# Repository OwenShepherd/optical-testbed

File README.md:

# AWESoMe Automation
Team: **A**pparatus for **W**avefront **E**rror **S**ens**o**r **Me**asurement

Website: [AWESoMe](https://www.colorado.edu/aerospace/current-students/undergraduates/senior-design-projects/past-senior-projects/2017-2018/apparatus)  

AWESoMe is a joint project between the South West Research Institute (SWRI) and a team of Aerospace Engineering students at Boulder.  The goal of the project is to create a testbed for comparing the performance of a [Shack-Hartmann Array](https://en.wikipedia.org/wiki/Shack%E2%80%93Hartmann_wavefront_sensor) (SHA) and a [Roddier Curvature Wavefront Sensor](http://www.soft.belastro.net/files/tmp/Wave-front_reconstruction_from_defocused_images_and_the_testing_of_ground-based_optical_telescopes.pdf) (RCWS).  

This repository contains .NET programs aimed at automating as much of the testbed as possible due to the large number of tests that need to be run in a timely manner.  This mostly includes: prompting the user to load in a specifically formatted CSV for scheduling tests, and then running those tests one-by-one by adjusting the parameters of the SHA, RCWS, and motorized stages.

## Getting Started
Some third-party drivers and Visual Studio 15 need to be installed.

### Pre-Requisites  
**Please download drivers as 32-bit or it may cause some compatibility issues**  

First, ensure you have at least Visual Studio 15 installed (or at least 10.0.40219.1).  Then, install the following drivers in the listed order:
- [ASI120MM Drivers](http://astronomy-imaging-camera.com/software/)
- [ASCOM Platform 6.3](https://ascom-standards.org/Downloads/Index.htm)
- [ASCOM Platform Developer Components](https://ascom-standards.org/Downloads/PlatDevComponents.htm)
- [ASI Cameras ASCOM Driver](http://astronomy-imaging-camera.com/software/)
- [QHY Camera Driver](http://www.qhyccd.com/QHY5-III-Camera.html)
- [QHY ASCOM Driver (Capture Version V0131)](http://www.qhyccd.com/ASCOM-Camera.html)

Next, in order to use the complete version of the program, the most recent version of Python (At least Python version 3.6) must be installed:
- [Python Downloads](https://www.python.org/downloads/)

Then, install pyserial for Python 3 in any fashion (reccomended to use pip); just ensure that pyserial can be called from a Python 3 program:
- [Pyserial](https://pypi.python.org/pypi/pyserial)

Next, the program requires extra DLLs in order to run properly.  These must be acquired by also installing the following software:
- [Thorlabs Kinesis (32-bit for 32-bit or 32-bit for 64-bit](https://www.thorlabs.com/software_pages/ViewSoftwarePage.cfm?Code=Motion_Control&viewtab=0)
- [Thorlabs WFS](https://www.thorlabs.com/software_pages/ViewSoftwarePage.cfm?Code=WFS)

Lastly, it is possible that the software will initially have issues connecting to the QHY due to a defect in the driver.  In this event, it is required to use sharpcap to connect to the QHY via ASCOM, and simply set the gain to, say, 1, and click accept.  It is possible that some error warnings will pop up, but ignore these.  Try running your experiment again and see if an error still pops up about some camera connection issues.
- [Sharpcap](https://www.sharpcap.co.uk/sharpcap/downloads)

## Running the Program
As of now, the program has been tested with all components of the testbed and is working in its designed fashion for data collection.  The most recent working version of the program is contained in the "TestBed_Automation_Final" Visual Studio Project.  The installer for the project builds may be found at [this link](https://drive.google.com/open?id=1Bk6WBR5vOVbcDDSYLsn6n1ccp4iNH_cr) (NOTE: Only CU Boulder Accounts may access this link).

### Using the Executable
The Visual Studio Project will automatically add the required files for the executable to the appropriate directory.  But, when running the executable outside of visual studio, ensure that the following are in the same directory as the EXE:
- ASCOM.DeviceInterfaces.dll
- ASCOM.DriverAccess.dll
- ASCOM.Exceptions.dll
- ASCOM.Utilities.dll
- SerialReader.py
- Thorlabs.MotionControl.DeviceManager.dll
- Thorlabs.MotionControl.DeviceManagerCLI.dll
- Thorlabs.MotionControl.GenericMotorCLI.dll
- Thorlabs.MotionControl.KCube.DCServo.dll
- Thorlabs.MotionControl.KCube.DCServoCLI.dll
- Thorlabs.MotionControl.Tools.Common.dll
- Thorlabs.MotionControl.Tools.Logging.dll
- Throlabs.WFS.Interop.dll

An official "release" hasn't been made yet for this program, although running the program in Visual Studio will achieve the desired results.

## Data Organization
This is how data is organized by the program.

### Filesystem Organization
Here is how data will be organized.  An experiment corresponds to a collection of data
taken during one session.  Each state corresponds to a different test (i.e. with
different de-focus distances, exposures, etc...).
```
EXAMPLE_EXPERIMENT
├── 2018_02_03_13_48_41_STATE1
├── 2018_02_03_13_50_55_STATE2
├── 2018_02_03_13_52_13_STATE3
├── 2018_02_03_13_54_32_STATE4
│   ├── data_RCWS
│   │   ├── img_RCWS_aft.png
│   │   ├── img_RCWS_fore.png
│   │   └── zernikes_RCWS.csv
│   ├── data_SHA
│   │   ├── img_SHA_aft.png
│   │   ├── img_SHA_fore.png
│   │   ├── spt_SHA_aft.png
│   │   ├── spt_SHA_fore.png
│   │   ├── wft_SHA_aft.png
│   │   ├── wft_SHA_fore.png
│   │   └── zernikes_SHA.csv
│   ├── env_data.csv
│   ├── state_parameters.csv
│   └── zernikes_model.csv
└── experiment_schedule.csv
```
The automation program will automatically create the experiment directory (as named off user input), and will automatically create the state folders based on the number of tests in the schedule file.  Each state folder will be filled with the appropriate data shown above as the tests are run.

### Schedule File Structure
The experiment_schedule.csv file will specify all the system states that are to be tested for a given experiment. For each state specified in this file the automated test control program will create the appropriate sub-folder of the test and populate it with the data that is produced while the experiment is running. In post-processing other files can be added in the created file structure. The first row will include the header:  
```
RCWS EXPT (us), SHA EXPT (us), RCWS D FORE (um), RCWS D AFT (um), M2 A X (arc sec), M2 A Y (arc sec)  
```
After that line every row of data will specify those state values at which to make a wavefront measurement with both sensors.

### Environmental Sensor Data
Data is collected from the environmental sensors and sent in an organized way to the computer.  Each set of data sent contains at most: 3-Dimensional readings from 6 accelerometers, and temperature readings from 6 IC temperature sensors.
```
| 0xA0 | 0xA1 | RT | SN | {PL} | SH | SL | MH | ML | UH | UL | CS | 0x0D | 0x0A |
```
These bytes / sets of bytes contain the following data:
- RT: (0 or 1) indicates whether the payload contains accelerometer or temperature data.
- SN: Indicates the sensor number / sensor ID
- PL: The actual sensor data; details below
- SH: MSB for seconds elapsed
- SL: LSB for seconds elapsed
- MH: MSB for milliseconds elapsed
- ML: LSB for milliseconds elapsed
- UH: MSB for microseconds elapsed
- UL: LSB for microseconds elapsed
- CS: Result of taking XOR of all payload and timestamp bytes.  AKA: A rudimentary checksum.

**Payload Organization**:  
Temperature Sensor:
```
| Temperature High Byte | Temperature Low Byte |
```

Accelerometer:
```
| Acc. Axis 1 H | Acc. Axis 1 L | Acc. Axis 2 H | Acc. Axis 2 L | Acc. Axis 3 H | Acc. Axis 3 L |
```

## Conceptual Information

### ASCOM References
The two RCWS cameras (ASI120MM & QHY...) both interface with Windows using ASCOM.  Some
references on how to use ASCOM with VS:
- [ASCOM Standards](http://www.ascom-standards.org/Help/Developer/html/7d9253c2-fdfd-4c0d-8225-a96bddb49731.htm)

### ASEN_RCWS class
The ASEN_RCWS class can be used to take images and save them in a very simple
way.  Currently, it has only been tested with the ASI, but should be able to
easily extend to the QHY if necessary.  To use the class, follow the current
example shown in the "program.cs" file for using the ASI120MM.

### ASEN_KDC Class
In order for the current test code for the KDC101 to work, you must do the
following.  Currently the class is not ready as further testing needs to be
completed.

Add these references to the program (if they are not already included):
- Thorlabs.MotionControl.KCube.DCServoCLI.dll
- Thorlabs.MotionControl.DeviceManagerCLI.dll
- Thorlabs.MotionControl.GenericMotorCLI.dll

In addition, the following native C DLLs need to be copied to the executable folder:
- ThorLabs.MotionControl.KCube.DCServo.dll
- ThorLabs.MotionControl.DeviceManager.dll

These DLL files may be found in the References_DLL/KDC101 folder.

## Authors (This Repository)
- Owen Shepherd
- Jake Crouse

## The Team
- Robert Belter
- Ali Colic
- Jake Crouse
- Lucas Droste
- Diego Gomes
- Ankit Hriday
- Owen Lyke
- Brandon Noirot
- Owen Shepherd
- Brandon Stetler

## Acknowledgements
- Eliot Young (SWRI)
- Bob Woodruff (SWRI)
- Engineering Excellence Fund (EEF)
- NASA Glenn

## ASEN 4018 - Senior Projects Environmental Sensors Code
This code was used to test the following devices and conduct experiments with
the following software as well as accelerometers and thermometers.

The code is located in root/env_sensors.

### Software Used
* Arduino IDE 1.8.5
* SDFat Version 1.0.3
* TeensyDuino Version 1.40
* DallasTemperature Version 3.7.6
* Python 3.6.2
* pySerial 3.4

### Software Downloads
* [Arduino IDE](https://www.arduino.cc/en/Main/Software)  
* [TeensyDuino](https://www.pjrc.com/teensy/td_download.html)  
* [SDFat Repository](https://github.com/greiman/SdFat)
* [pySerial](https://pypi.python.org/pypi/pyserial)
* [Python](https://www.python.org/downloads/)

### Installation
Download and install the Arduino IDE along with the TeensyDuino
addon.  Then, download SDFat Version 1.0.3 and DallasTemperature using the
library manager in the IDE, and then you can open "ASEN-4018-EnvSensors.ino"
located in the root directory using the Arduino IDE.  

To use the custom libraries made for the project, either
copy the folders in "LocalLib" to the Arduino libraries folder at the root of
your sketches directory or (what I did for easier git integration): create
symbolic links to the folders in "LocalLib" and place those shortcuts in the Arduino
libraries folder.  NOTE: This was mostly developed in Ubuntu; Windows users should 
note that shortcuts != symoblic links.  I have not tested development on a Apple
computer.

### Filesystem Info
Function details (.h) and their implementations (.cpp) are
located in their respective header and implementation files within "LocalLib/".
The current functions provide ADXL reading, SD Performance estimates, and SD
implementations.  

### Testing information
Please read "RateTesting.md" in the root of the git directory for information
about how to test the Teensy for various data rate performances.

### Examples Used to Develop Code
* [Speeding UP SD Writes](https://forum.arduino.cc/index.php?topic=49649.0)
* [Low-Latency Logger Example](https://github.com/greiman/SdFat/tree/master/examples/LowLatencyLogger)
* [Using an ADXL345 with the Teensy](https://gist.github.com/FuzzyWuzzie/b1903a8353dc1ec57da8)
* [Using DS18B20 Temp. Sensor with Arduino](https://create.arduino.cc/projecthub/TheGadgetBoy/ds18b20-digital-temperature-sensor-and-arduino-9cc806)

### Examples
To test Teensy SD read / write performance:
```
#include "TeensySDPerformance.h"

void setup() {
  perfSetup();
}

void loop() {
  perfLoop();
}  
```

To read temperature from pin 1 on the Teensy and save it to the SD card:
```
#include "temp.h"
#include <string>

String filename = "TemperatureReadings.csv";

void setup() {
  tempSetup();

}

void loop() {
  tempLoop(filename);
}
```

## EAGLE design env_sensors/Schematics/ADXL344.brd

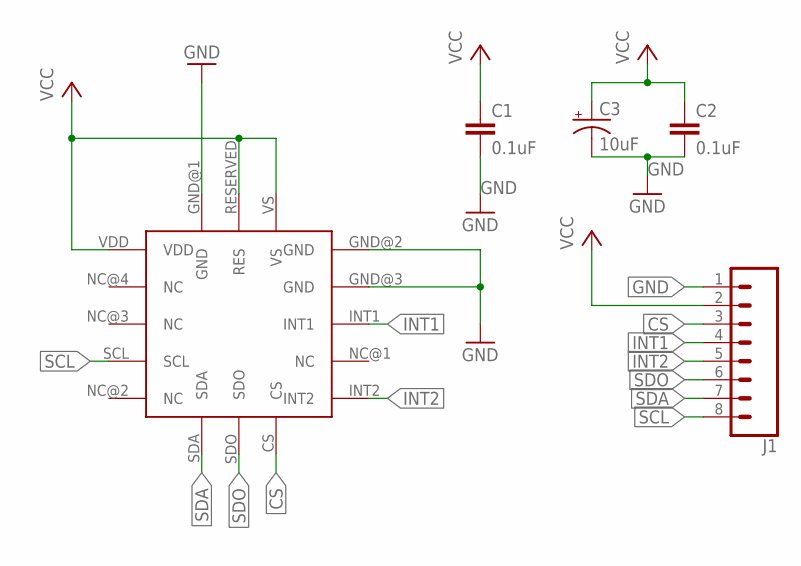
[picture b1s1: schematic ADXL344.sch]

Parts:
ADXL1: ADXL344ADXL-C; ADXL-C
C1, C2: 0.1uF; 0603
C3: 10uF; 0603-POLAR
J1: CONN_08"; 1X08

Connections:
CS: ADXL1.CS, J1.3
GND: ADXL1.GND@1 (GND), ADXL1.GND@2 (GND), ADXL1.GND@3 (GND), C1.2, C2.2, C3.-, J1.1
INT1: ADXL1.INT1, J1.4
INT2: ADXL1.INT2, J1.5
SCL: ADXL1.SCL, J1.8
SDA: ADXL1.SDA, J1.7
SDO: ADXL1.SDO, J1.6
VCC: ADXL1.RESERVED (RES), ADXL1.VDD, ADXL1.VS, C1.1, C2.1, C3.+, J1.2

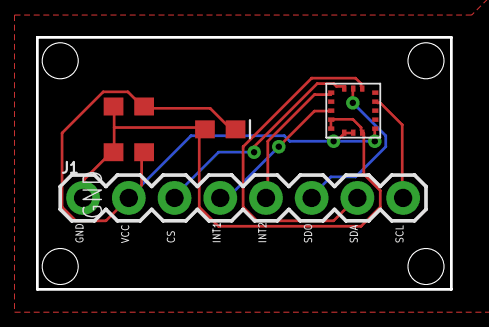
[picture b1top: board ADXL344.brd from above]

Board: 2 copper layers, 23.0 x 14.0 mm, 5 parts (0 on the bottom side), 8 nets.

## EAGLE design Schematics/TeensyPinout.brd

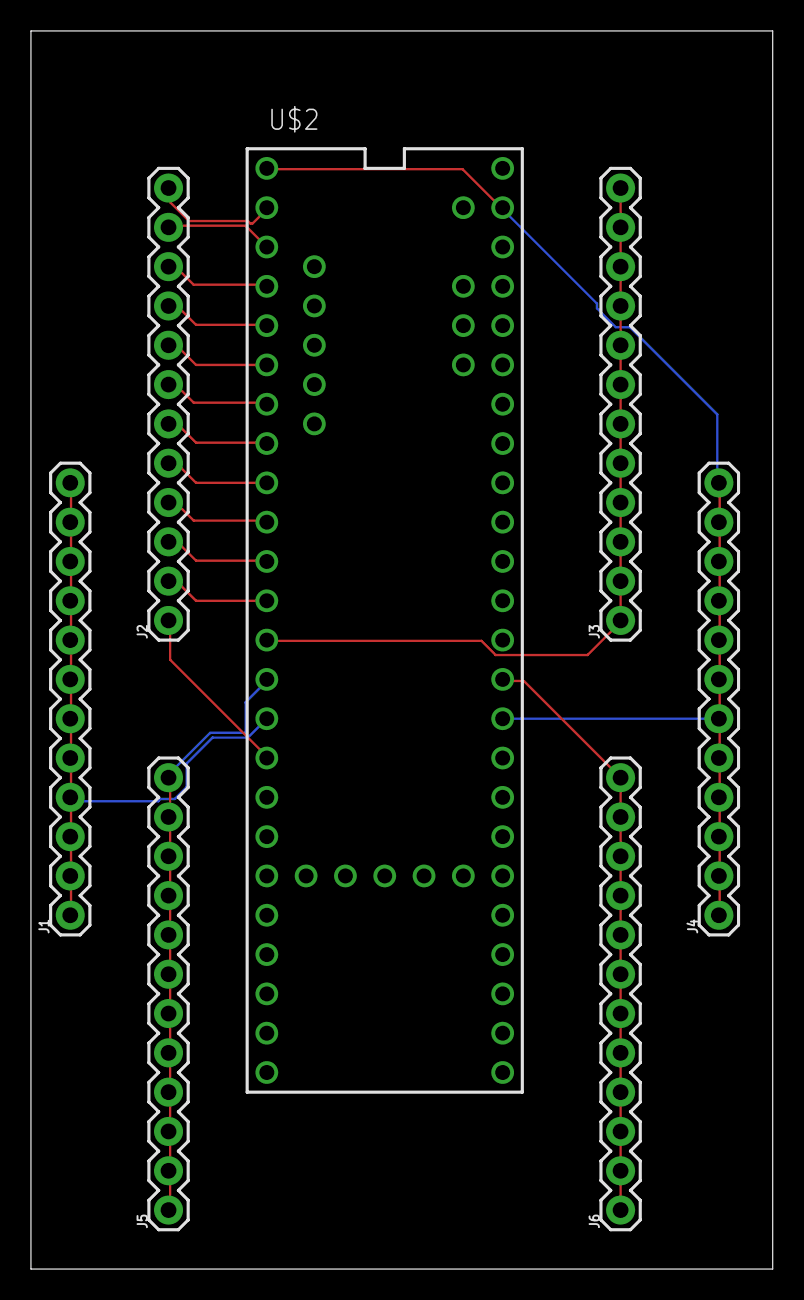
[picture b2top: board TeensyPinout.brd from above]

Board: 2 copper layers, 47.9 x 80.0 mm, 7 parts (0 on the bottom side), 17 nets.

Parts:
J1, J2, J3, J4, J5, J6: 1X12
U$2: TEENSY-3.6_ONLY_HOLES

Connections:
GND: J4.1, J4.2, J4.3, J4.4, J4.5, J4.6, J4.7, J4.8, J4.9, J4.10, J4.11, J4.12, U$2.AGND, U$2.GND1, U$2.GND2
MISO: J5.1, J5.2, J5.3, J5.4, J5.5, J5.6, J5.7, J5.8, J5.9, J5.10, J5.11, J5.12, U$2.12
MOSI: J3.1, J3.2, J3.3, J3.4, J3.5, J3.6, J3.7, J3.8, J3.9, J3.10, J3.11, J3.12, U$2.11
unnamed: J2.12, U$2.0
unnamed: J2.10, U$2.2
unnamed: J2.9, U$2.3
unnamed: J2.11, U$2.1
unnamed: J2.8, U$2.4
unnamed: J2.7, U$2.5
unnamed: J2.6, U$2.6
unnamed: J2.5, U$2.7
unnamed: J2.4, U$2.8
unnamed: J2.3, U$2.9
unnamed: J2.2, U$2.10
unnamed: J2.1, U$2.24
SCK: J6.1, J6.2, J6.3, J6.4, J6.5, J6.6, J6.7, J6.8, J6.9, J6.10, J6.11, J6.12, U$2.13
VCC: J1.1, J1.2, J1.3, J1.4, J1.5, J1.6, J1.7, J1.8, J1.9, J1.10, J1.11, J1.12, U$2.3V3_1

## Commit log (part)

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2017-11-09 Collected possible examples / took Greiman's source code for analysis
2017-11-09 Added proper Teensy pins to macros and created some initial functions
2017-11-09 Added README and some library / software information
2017-11-09 Added info. Really just testing git.
2017-11-09 Refactored ADXL code some. Added a new struct for storing acceleration readings.
2017-11-09 Re-did the filesystem so that hopefully the Arduino IDE will work better with it
2017-11-09 Re-arranged the example code into header files and removed the old ADXL files.
2017-11-09 Created header / implementation from SD card performance examples.
2017-11-09 Further documentation details.
2017-11-09 Insignificant commit. Ignore.
2017-11-09 Cleaned up headers for implementation and added performance to the header files.
2017-11-11 Updating libraries. Can now check teensy SD performance.
2017-11-11 Updated Readme documentation to explain custom library integration.
2017-11-11 Clean up Readme some more.
2017-11-11 Re-arranged readme.
2017-11-13 Added a library to work with the DS18B20. Currently giving a wrong value with 10kohm pullup - will try 4.7kohm ASAP.
2017-11-13 Updated readme with a temperature code example
2017-11-14 Created short script for writing test txt files. Gonna move on to CSV probably next.
2017-11-14 Able to save temperature readings as a CSV file on the SD card. Can be read from computer as well.
2017-11-14 Teensy saves temperature readings to CSV file with timestamp.
2017-11-14 Can now measure write times, which are currently inadequate. A fix is known and will hopefully be relatively easy to implement. Added link to README.
2017-11-14 Updated Readme.
2017-11-28 First ADXL attempts with data rate changed.
2017-11-30 Updated SD code for benchmarking.
    Messing with the main sketch file to try and get final results for the SD being used with a temperature sensor.
2017-12-01 Serial Read and Data Check
    Python script "readSerial.py" now reads from a teensy given some initial parameters.
2017-12-01 Updated Serial Read testing documentation
2017-12-01 Further Documentation
    updated README to include info about the testing
2017-12-01 Added Simple Plotter
    Simple plotter for the rate testing data has been added. Will be improved.
2017-12-03 Updated Testing Files
    Updated some of the documentation, made the filesystem more organized, data better ready for further adjustments.
2017-12-13 Added extra documentation detailing new software.
2017-12-18 Updating the repository with electronic schematics.
2017-12-18 Added info about SPI Tests
2018-01-29 Simply forgot a line.
2018-02-03 Added current filesystem structure to the README.
2018-02-05 Quick testing
2018-02-06 Added a good reference I finally found for ASCOM
2018-02-06 Creating .ignore
    This .gitignore file was taken from https://github.com/github/gitignore/blob/master/VisualStudio.gitignore
2018-02-06 Added some installation steps to the README
2018-02-06 Added team webiste
2018-02-09 Created new class to abstract the somewhat complicated camera API class for the ASCOM stuff.
    Created a new class ASEN_RCWS in order to facilitate more streamlined image captures / RCWS camera work. Testing on new class not done yet, but syntactically sound as of now.
2018-02-11 New class tested and works
    New class simplifies the camera process. Saving to CSV is currently commented out until file path stuff is fixed...
2018-02-11 Updated the README for the new ASEN_RCWS class
2018-02-26 Squashed initial bugs
    SHA class file listed under "SHA.cs"
2018-02-27 Added some testable code and fixed reference issues
2018-02-27 Updated readme with reference info.
2018-02-27 Cleaned up the repository and added proper DLLs
2018-02-27 Updated README with DLL info
2018-02-27 Final saves......
2018-02-28 Added some info about the KDC and the 32-bit problems
2018-02-28 Solution stored in "WFS150-7AR" folder is now capable of interfacing with SHA.
    Although the exact problems that were occuring with the DLL are still unknown, it seems that the "Thorlabs.WFS.Interop64" DLL had a reference to a 32 bit DLL and was causing issues when VS would run 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
2018-02-28 Added jakeTest.cs
    jakeTest.cs is a lot of the work Jake did on the SHA and has useful comments that explain the SHA process. I'm gonna delete his working branch now as we have the SHA working.
2018-02-28 Added experiment name input functionality
    Users are now prompted to enter the name of an experiment.
2018-02-28 Now the SHA and RCWS data subfolders are created
    The data subfolders are automatically created.
2018-02-28 Added a simple GUI to prompt the user to select a folder path
    The GUI includes a simple windows form with a "select directory" button and an "exit" button. It's pretty rudimentary right now.
2018-03-01 Refined the main window
2018-03-01 Added correct jakeProgram file
2018-03-01 Changed behavior of the start button
    Also starting to add the ability to read the CSV files.
2018-03-01 Re-formatted README before it got worse
2018-03-01 Fixed grammar errors and added more filesystem info
2018-03-01 Added in Ability to Change Exposure Time and Master Gain
    Previously, the SHA was automatically setting the exposure time and gain, but we want to control these variables. So, I added in the ability for the program to write the exposure time and gain ranges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
2018-03-01 Update README.md
    just formatting....
2018-03-01 Program is ready to call separate methods
    The GUI now parses the CSV as chosen by the user and is ready to pass that data onto the necessary SHA, motor, RCWS, and Teensy methods.
2018-03-02 Added selection box
    Unprogrammed selection box will let user specify whether they are using the QHY or the ASI camera.
2018-03-02 Added new classes
    Attempting to organize the program better. Now the start button collects path information into strings and calls a new class called "Experiment" which tries to handle the experiment-level processes (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
2018-03-02 Added a dropdown menu
    Drop down menu for selecting the camera in use has been added...committed to wrong repository.
2018-03-04 Fixed most ASEN_SHA class bugs.
    Dropped the error count from 66 to 6, so most have been squashed. I still need to learn how to use the constructor, so I'll work on that a bit more.
2018-03-04 Fixed the ASEN_SHA constructor.
    I didn't understand how to use the constructor from a derived class, but I figured it out.
2018-03-05 Optimized code for automation, but created an error with the constructor.
    Optimized the code for automation, which meant removing a lot of the user-specified values and replacing them with either hard-coded values or values coming from experiment_schedule.csv. In the proce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
2018-03-08 Initial Completion of ASEN_SHA, needs to be verified on Hardware.
    I have completed the ASEN_SHA class, but it needs to be verified on the SHA hardware at SWRI before this can be confirmed. I simply went through the code and configured all the functions to run as we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
2018-03-08 Created a new program to test the ASEN_SHA class in an implementation.
    This added function calls the ASEN_SHA functions in an attempt to take the spotfield image and calculate the Zernikes.
2018-03-08 Added RCWS implementation to state class
    I have it commented out still, as I will finely examine it before testing.
2018-03-08 Verified ASEN_SHA at SwRI.
    The SHA works with the ASEN_SHA class. This was tested as SwRI.
2018-03-09 Expanding motor control class and adding documentation
    Added documentation to local files cause it got tiring searching through Thorlabs' convoluted file structure. Also, motor control functionality / the motor control class is being expanded.
2018-03-09 Added motor control and image control to the loop
    Code is still commented out to just showcase that it is untested, but as far as I know it should be good to go before I test next time I'm in lab.
2018-03-09 Initial environmental sensors class structure
2018-03-09 Filled out the methods in the ASEN_ENV class
2018-03-09 Solution file was updated
2018-03-09 Added further functionality to the motor class.
2018-03-09 Added threading, cleaned up classes
    Still need to get the conversion down for the motor classes, but threading and parallelization are (likely) ready to go. Also changed the file structure for better organization and started to add cor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
2018-03-09 Changed the Solution name
2018-03-09 Changed the folder name too....
2018-03-13 Added teensy locks
    I'm not sure on the C# "tasks" class, but I'm guessing for proper async tasks I'll need to lock the boolean that controls whether or not the Teensy should continue reading.
2018-03-13 Added references for each API
    References are listed under the Refernces/DLL folder in the root of the git repository.
2018-03-14 Little bit of on-site troubleshooting
2018-03-16 Working through ENV code
2018-03-19 Making more progress on the motor control units
2018-03-23 Added event handlers for serial data
2018-03-24 Using serial read by launching python externally. Much simpler than IronPython
2018-04-02 Whew. Added ipython and python path selection for proper running.
    Added new inputs to the classes as well. This is gonna need a cleanup....
2018-04-03 Deleted worthless "deploy" folder
2018-04-03 Made appropriate DLLs automatically added to .EXE folder
2018-04-05 Finished initial creation of the QHY class and methods.
2018-04-05 Fixed file naming and deletion in the QHY class.
2018-04-05 Added initial functions for controlling testbed with asi vs. qhy
2018-04-05 Added initialization parts to the runstate method
    Also add new methods to the motor control path.
2018-04-05 QHY and ASI methods in the state class are mostly done.
    Still need to add control of the SHA to the methods as of now.
2018-04-05 Added method to SHA class for taking a spotfield image.
    Not a complicated addition luckily.
2018-04-05 Wavefront saving is complete.
2018-04-05 Added image saving to the proper SHA methods.
    These all take place within the class, only minor changes to state class needed now (to pass filenames to the SHA class).
2018-04-05 Added the qhyccd.dll for the QHY API to the solution.
2018-04-07 Fixed minor file-saving path error
    I appended the filepath in the SHA API improperly. Just a small fix.
2018-04-07 Increased length of QHY memory
    The example allocated arrays to 3 times the value returned by memlength. Could this be because they also got heap corruption errors and this was their fix? Possibly....
2018-04-10 Updated the README
    As the project is much more complete to this point. The README required a little bit of updating.
2018-04-17 Checks to see if mirror should be moved.
    Also all units are converted correctly.
2018-04-21 Adding the SNR_Calc
2018-04-22 Fixed some of the SNR_calc stuff
2018-04-22 TestData updated.
2018-04-22 SNR Calc close to completion
2018-04-22 SNR Calcs completed
    SNR calculations are now performed by SNR_calc2.py
2018-04-22 Readme prequisites filled out
    All prerequisites to get the software running are now listed.
2018-04-22 Added sharpcap download.
2018-04-24 Added links, automatic updating of parameters.
2018-05-07 Removed extraneous html docs for other libraries.
2021-08-11 Env sensors code moved to its own directory. README changed.

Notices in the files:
parts and their libraries:
SparkFun-Connectors: Licensing: Creative Commons ShareAlike 4.0 International - https://creativecommons.org/licenses/by-sa/4.0
